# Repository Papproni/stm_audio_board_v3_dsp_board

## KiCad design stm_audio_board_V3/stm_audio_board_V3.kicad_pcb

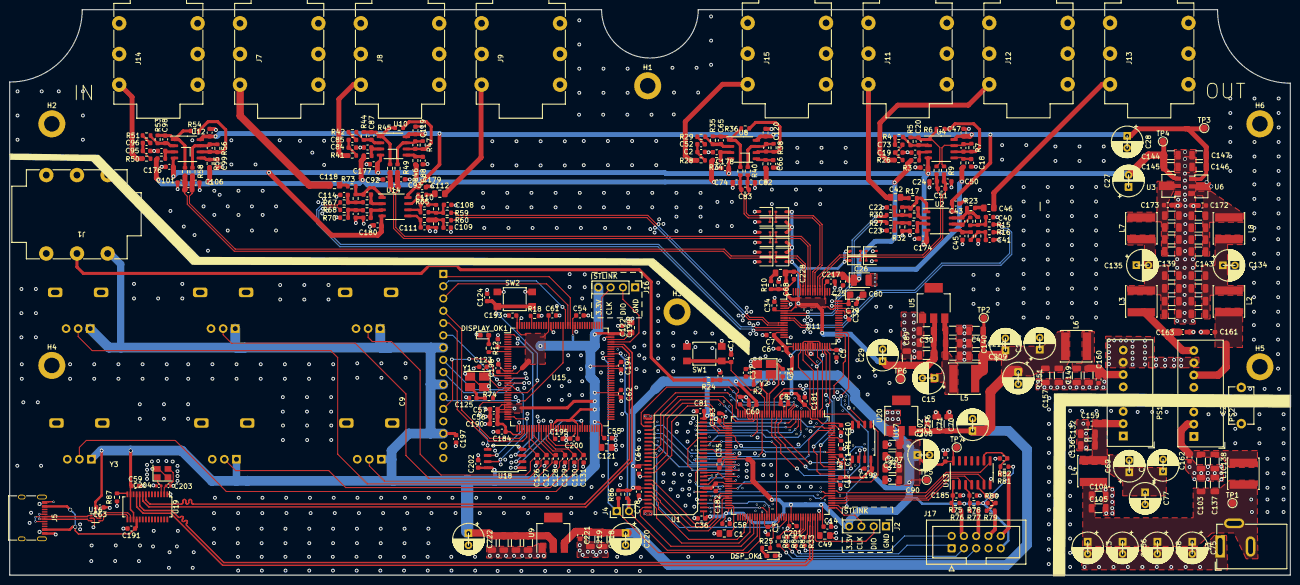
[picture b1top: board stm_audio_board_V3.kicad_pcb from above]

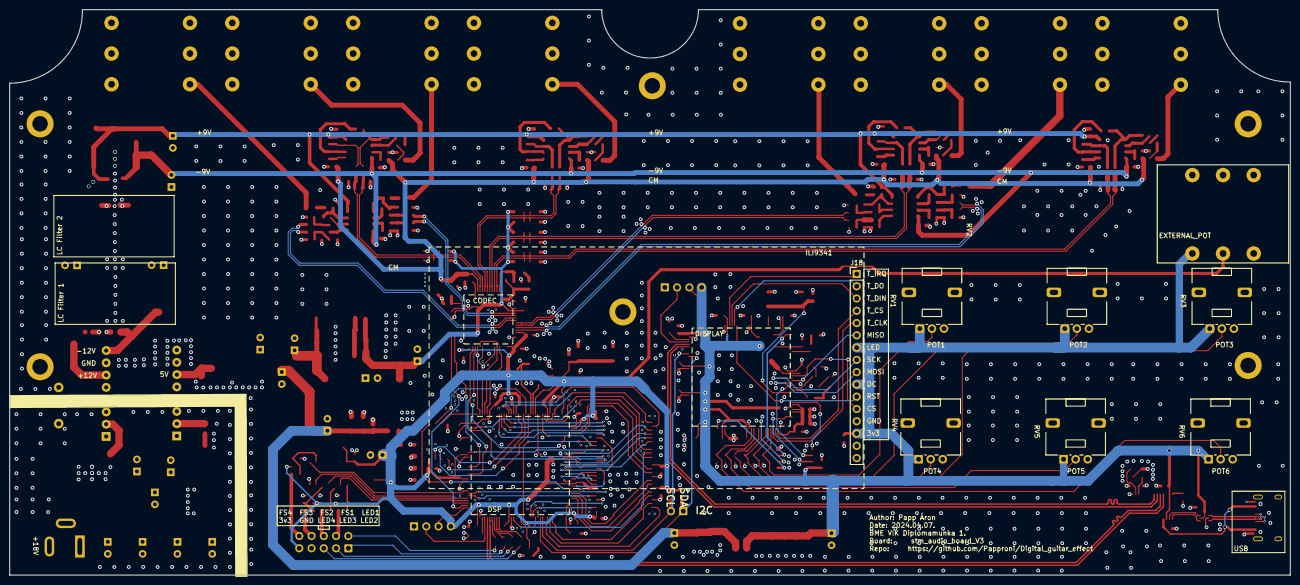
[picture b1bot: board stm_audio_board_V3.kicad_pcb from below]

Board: 4 copper layers, 265.0 x 117.0 mm, 404 parts (7 on the bottom side), 232 nets.

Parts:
C1, C42, C46, C49, C112, C118, C121, C122: 2.2uF; C_0805_2012Metric_Pad1.18x1.45mm_HandSolder
C2, C19, C21, C38, C39, C44, C45, C51, C72, C83, C84, C91, C94, C95, C100, C107, C110, C111, C116, C117: 100pF; C_0603_1608Metric
C3, C5, C6, C7, C8, C9, C10, C11, C12, C14, C16, C17, C18, C25, C32, C33, C34, C35, C36, C43, C47, C52, C53, C54, C55, C56, C57, C58, C59, C60, C61, C62, C63, C64, C66, C73, C78, C79, C81, C85, C86, C88, C96, C97, C99, C102, C113, C119, C120, C124, C126, C127, C128, C129, C130, C131, C159, C160, C161, C162, C163, C172, C173, C174, C175, C176, C177, C178, C179, C180, C181, C182, C183, C184, C185, C186, C187, C188, C189, C190, C191, C192, C193, C194, C195, C196, C197, C198, C199, C200, C201, C202, C217, C221, C227: 100nF; C_0603_1608Metric
C4, C30, C71, C89, C90, C103, C104, C105, C132, C133, C136, C137, C138, C139, C141, C142, C143, C144, C145, C146, C147, C148, C149, C152, C153, C154, C155, C157, C158, C164, C165, C166, C167, C168, C169, C170, C171, C205, C206, C207, C209, C210, C211, C212, C213, C214, C215, C216, C218, C219, C223, C224, C225, C226: 10uF; C_1206_3216Metric
C13, C15, C27, C28, C29, C48, C69, C70, C75, C76, C77, C134, C135, C140, C150, C151, C156, C208, C220, C222: 100uF; CP_Radial_D6.3mm_P2.50mm_reference_fix
C20, C65, C87, C98: 1p; C_0603_1608Metric
C22, C23, C40, C41, C108, C109, C114, C115: 470pF; C_0603_1608Metric
C24, C50, C68, C74, C82, C92, C93, C101, C106, C228: 1nF; C_0603_1608Metric
C26: 100uF tantal; CP_EIA-3528-21_Kemet-B
C31, C37, C123, C125: 12pF; C_0603_1608Metric
C67: 33nF; C_0805_2012Metric_Pad1.18x1.45mm_HandSolder
C80: 10uF tantal; CP_EIA-3216-18_Kemet-A
C203, C204: 20pF; C_0402_1005Metric
C229: 1nF; C_Disc_D7.5mm_W5.0mm_P7.50mm
D1, D4, D5, D6, D7, D8, D9, D12, D13, D14, D15, D16, D17, D18, D19, D20: 1N5819; D_SOD-323
DISPLAY_OK1: LED; LED_0603_1608Metric_Pad1.05x0.95mm_HandSolder
DSP_OK1: LED; LED_0603_1608Metric_Pad1.05x0.95mm_HandSolder
H1, H2, H3, H4, H5, H6: MountingHole_Pad; MountingHole_3.2mm_M3_DIN965_Pad
J1: External_POT; 6.3_jack_new_ref
J2: STlink_DSP; PinHeader_1x04_P2.54mm_Vertical
J3: Barrel_Jack_Switch; BarrelJack_GCT_DCJ200-10-A_Horizontal
J4: Conn_01x02_i2c; PinHeader_1x02_P2.54mm_Vertical
J5: USB_C_Receptacle_USB2.0; USB_C_Receptacle_XKB_U262-16XN-4BVC11
J7: AudioJack_LOOP1_SEND; 6.3_jack_new_ref
J8: AudioJack_LOOP1_RETURN; 6.3_jack_new_ref
J9: AudioJack_LOOP2_SEND; 6.3_jack_new_ref
J11: AudioJack_LOOP3_SEND; 6.3_jack_new_ref
J12: AudioJack_LOOP3_RETURN; 6.3_jack_new_ref
J13: AudioJack_OUTPUT; 6.3_jack_new_ref
J14: AudioJack_INPUT; 6.3_jack_new_ref
J15: AudioJack_LOOP2_RETURN; 6.3_jack_new_ref
J16: STlink_DISP_MCU; PinHeader_1x04_P2.54mm_Vertical
J17: Conn_01x10_Footswitch; IDC-Header_2x05_P2.54mm_Vertical
J18: Conn_01x16_ILI9341; PinHeader_1x16_P2.54mm_Vertical
L1, L2, L3, L4, L5, L6, L7, L8: 10uH; L_Sunlord_SWPA6020S
PS1: URB2405S-6WR3; Converter_DCDC_XP_POWER-ITxxxxxS_THT
PS2: WRA2412S-3WR2; Converter_DCDC_XP_POWER-ITxxxxxS_THT
R1, R18, R75, R78, R80, R82: 10k; R_0603_1608Metric
R2, R3, R8, R9, R11, R24, R26, R28, R34, R37, R39, R40, R41, R43, R46, R48, R49, R50, R52, R55, R57, R58, R74: 100R; R_0603_1608Metric
R4, R29, R42, R51: 1M; R_0603_1608Metric
R5, R35, R44, R53: 510k; R_0603_1608Metric
R6, R7, R36, R38, R45, R47, R54, R56: 4k7; R_0603_1608Metric
R10, R13, R14, R15, R16, R19, R20, R21, R22, R27, R30, R31, R32, R59, R60, R61, R62, R63, R64, R66, R67, R68, R69, R70, R71, R72, R86: 3k; R_0603_1608Metric
R12, R17, R23, R25, R33, R65, R73, R76, R77, R79, R81, R83, R84, R85: 1k; R_0603_1608Metric
R87: 2.7k; R_0603_1608Metric
RV1, RV2, RV3, RV4, RV5, RV6: R_Potentiometer; Potentiometer_Alps_RK09L_Single_Vertical
SW1, SW2: SW_SPST; SW_SPST_TL3305A
TP1: TestPoint_PWR_IN; TestPoint_Pad_D1.5mm
TP2: TestPoint_5V; TestPoint_Pad_D1.5mm
TP3: TestPoint_9V; TestPoint_Pad_D1.5mm
TP4: TestPoint_-9V; TestPoint_Pad_D1.5mm
TP5, TP7: TestPoint_3V3; TestPoint_Pad_D1.5mm
TP6: TestPoint_3V3A; TestPoint_Pad_D1.5mm
U1: IS42S16100H-7TL; TSOP-2-50-new
U2, U4, U8, U10, U12, U14: OP275; SSOP-8_3.9x5.05mm_P1.27mm
U3: 7909; SOT-89-3
U5, U9, U20: AP1117-33; SOT-223
U6: 7809; SOT-89-3
U7, U15: STM32H723ZGTx; LQFP-144_20x20mm_P0.5mm
U11: LQFP-64_10x10mm_P0.5mm
U13: 74HC14; SOIC-14_3.9x8.7mm_P1.27mm
U16: USBLC6-2P6; SOT-666
U17, U18: W25Q128JVS; SOIC-8_5.23x5.23mm_P1.27mm
U19: FE1.1s; SSOP-28_3.9x9.9mm_P0.635mm
Y1, Y2: X1E0000210132; Crystal_SMD_SeikoEpson_TSX3225-4Pin_3.2x2.5mm_HandSoldering
Y3: Crystal_GND24; Crystal_SMD_3225-4Pin_3.2x2.5mm

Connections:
5V: C4.1, C70.1, C71.1, C102.1, C140.1, C148.1, C150.1, C151.1, C157.1, C209.1, C210.1, C216.1, C218.1, C219.1, C220.1, C221.1, L5.1, L6.2, TP2.1, U9.3 (VI), U20.3 (VI)
+3.3V: C3.1, C5.1, C6.1, C7.1, C8.1, C9.1, C10.1, C11.1, C12.1, C14.1, C35.1, C36.1, C54.1, C55.1, C56.1, C57.1, C58.1, C59.1, C60.1, C61.1, C62.1, C63.1, C64.1, C78.1, C81.1, C90.1, C181.1, C182.1, C183.1, C184.1, C189.1, C190.1, C192.1, C193.1, C194.1, C195.1, C196.1, C197.1, C198.1, C199.1, C200.1, C201.1, C202.1, C207.1, C208.1, C214.1, C215.1, C222.1, C223.1, C224.1, C225.1, C226.1, J1.T, J2.4, J16.4, J17.9, J18.7, J18.10, J18.14, R66.1, R75.1, R78.1, R80.1, R82.1, R86.1, RV1.1, RV2.1, RV3.1, RV4.1, RV5.1, RV6.1, TP5.1, TP7.1, U1.1 (VDD), U1.7 (VDDQ), U1.13 (VDDQ), U1.25 (VDD), U1.38 (VDDQ), U1.44 (VDDQ), U7.6 (VBAT), U7.17 (VDD), U7.30 (VDD), U7.32 (VREF+), U7.33 (VDDA), U7.39 (VDD), U7.52 (VDD), U7.62 (VDD), U7.72 (VDD), U7.84 (VDD), U7.95 (VDD33USB), U7.108 (VDD), U7.121 (VDD), U7.131 (VDD), U7.144 (VDD), U9.2 (VO), U11.14 (PD/RST), U11.17 (DVDD), U11.32 (DVDD), U13.14 (VCC), U15.6 (VBAT), U15.17 (VDD), U15.30 (VDD), U15.32 (VREF+), U15.33 (VDDA), U15.39 (VDD), U15.52 (VDD), U15.62 (VDD), U15.72 (VDD), U15.84 (VDD), U15.95 (VDD33USB), U15.108 (VDD), U15.121 (VDD), U15.131 (VDD), U15.144 (VDD), U16.5 (VBUS), U17.8 (VCC), U18.8 (VCC), U19.13 (VD33), U19.17 (~XRSTJ), U20.2 (VO)
+3.3VA: C29.1, C30.1, C32.1, C33.1, C34.1, C68.1, C89.1, C205.1, C206.1, C217.1, C228.1, D4.1 (K), D5.1 (K), D7.1 (K), D9.1 (K), D13.1 (K), D15.1 (K), D17.1 (K), D19.1 (K), R10.2, TP6.1, U5.2 (VO), U11.5 (AVDD), U11.45 (AVDD), U11.51 (AVDD), U11.62 (AVDD)
+9V: C28.1, C43.1, C47.1, C113.1, C119.1, C120.1, C146.1, C147.1, C179.1, TP3.1, U2.8 (V+), U4.8 (V+), U6.1 (OUT), U8.8 (V+), U10.8 (V+), U12.8 (V+), U14.8 (V+)
-9V: C27.2, C144.1, C145.1, C174.2, C175.2, C176.2, C177.2, C178.2, C180.2, TP4.1, U2.4 (V-), U3.3 (VO), U4.4 (V-), U8.4 (V-), U10.4 (V-), U12.4 (V-), U14.4 (V-)
/Display_Interface/MCU_Display/DISPLAY_FLASH_CLK: U15.22 (PF10), U18.6 (CLK)
/Display_Interface/MCU_Display/DISPLAY_FLASH_CS: U15.64 (PE11), U18.1 (~CS)
/Display_Interface/MCU_Display/DISPLAY_FLASH_D0: U15.29 (PC3_C), U18.5 (DI(IO0))
/Display_Interface/MCU_Display/DISPLAY_FLASH_D1: U15.46 (PB0), U18.2 (DO(IO1))
/Display_Interface/MCU_Display/DISPLAY_FLASH_D2: U15.1 (PE2), U18.3 (IO2)
/Display_Interface/MCU_Display/DISPLAY_FLASH_D3: U15.35 (PA1), U18.7 (IO3)
/Display_Interface/MCU_Display/ILI9341_DISPLAY_CLK: J18.8, U15.19 (PF7)
/Display_Interface/MCU_Display/ILI9341_DISPLAY_CS: J18.12, U15.18 (PF6)
/Display_Interface/MCU_Display/ILI9341_DISPLAY_MISO: J18.6, U15.20 (PF8)
/Display_Interface/MCU_Display/ILI9341_DISPLAY_MOSI: J18.9, U15.21 (PF9)
/Display_Interface/MCU_Display/ILI9341_DISPLAY_RESET: J18.11, U15.125 (PG10)
/Display_Interface/MCU_Display/ILI9341_TOUCH_CLK: J18.5, U15.41 (PA5)
/Display_Interface/MCU_Display/ILI9341_TOUCH_CS: J18.4, U15.40 (PA4)
/Display_Interface/MCU_Display/ILI9341_TOUCH_IRQ: J18.1, U15.122 (PD6)
/Display_Interface/MCU_Display/ILI9341_TOUCH_MISO: J18.2, U15.124 (PG9)
/Display_Interface/MCU_Display/ILI9341_TOUCH_MOSI: J18.3, U15.123 (PD7)
/Display_Interface/MCU_Display/NRST_2: C124.1, SW2.1 (A), U15.25 (NRST)
/MCU/DSP_FLASH_CLK: U7.22 (PF10), U17.6 (CLK)
/MCU/DSP_FLASH_CS: U7.64 (PE11), U17.1 (~CS)
/MCU/DSP_FLASH_D0: U7.20 (PF8), U17.5 (DI(IO0))
/MCU/DSP_FLASH_D1: U7.21 (PF9), U17.2 (DO(IO1))
/MCU/DSP_FLASH_D2: U7.1 (PE2), U17.3 (IO2)
/MCU/DSP_FLASH_D3: U7.18 (PF6), U17.7 (IO3)
/MCU/DSP_SDRAM_ADRESS_BUS0: U1.21 (A0), U7.10 (PF0)
/MCU/DSP_SDRAM_ADRESS_BUS1: U1.22 (A1), U7.11 (PF1)
/MCU/DSP_SDRAM_ADRESS_BUS2: U1.23 (A2), U7.12 (PF2)
/MCU/DSP_SDRAM_ADRESS_BUS3: U1.24 (A3), U7.13 (PF3)
/MCU/DSP_SDRAM_ADRESS_BUS4: U1.27 (A4), U7.14 (PF4)
/MCU/DSP_SDRAM_ADRESS_BUS5: U1.28 (A5), U7.15 (PF5)
/MCU/DSP_SDRAM_ADRESS_BUS6: U1.29 (A6), U7.50 (PF12)
/MCU/DSP_SDRAM_ADRESS_BUS7: U1.30 (A7), U7.53 (PF13)
/MCU/DSP_SDRAM_ADRESS_BUS8: U1.31 (A8), U7.54 (PF14)
/MCU/DSP_SDRAM_ADRESS_BUS9: U1.32 (A9), U7.55 (PF15)
/MCU/DSP_SDRAM_ADRESS_BUS10: U1.20 (A10), U7.56 (PG0)
/MCU/DSP_SDRAM_ADRESS_BUS11: U1.19 (A11), U7.89 (PG4)
/MCU/DSP_SDRAM_CAS: U1.16 (/CAS), U7.132 (PG15)
/MCU/DSP_SDRAM_CKE: U1.34 (CKE), U7.29 (PC3_C)
/MCU/DSP_SDRAM_CLK: U1.35 (CLK), U7.93 (PG8)
/MCU/DSP_SDRAM_CS: U1.18 (/CS), U7.28 (PC2_C)
/MCU/DSP_SDRAM_DATA_BUS0: U1.2 (DQ0), U7.85 (PD14)
/MCU/DSP_SDRAM_DATA_BUS1: U1.3 (DQ1), U7.86 (PD15)
/MCU/DSP_SDRAM_DATA_BUS2: U1.5 (DQ2), U7.114 (PD0)
/MCU/DSP_SDRAM_DATA_BUS3: U1.6 (DQ3), U7.115 (PD1)
/MCU/DSP_SDRAM_DATA_BUS4: U1.8 (DQ4), U7.58 (PE7)
/MCU/DSP_SDRAM_DATA_BUS5: U1.9 (DQ5), U7.59 (PE8)
/MCU/DSP_SDRAM_DATA_BUS6: U1.11 (DQ6), U7.60 (PE9)
/MCU/DSP_SDRAM_DATA_BUS7: U1.12 (DQ7), U7.63 (PE10)
/MCU/DSP_SDRAM_DATA_BUS8: U1.39 (DQ8), U7.40 (PA4)
/MCU/DSP_SDRAM_DATA_BUS9: U1.40 (DQ9), U7.41 (PA5)
/MCU/DSP_SDRAM_DATA_BUS10: U1.42 (DQ10), U7.66 (PE13)
/MCU/DSP_SDRAM_DATA_BUS11: U1.43 (DQ11), U7.67 (PE14)
/MCU/DSP_SDRAM_DATA_BUS12: U1.45 (DQ12), U7.68 (PE15)
/MCU/DSP_SDRAM_DATA_BUS13: U1.46 (DQ13), U7.77 (PD8)
/MCU/DSP_SDRAM_DATA_BUS14: U1.48 (DQ14), U7.78 (PD9)
/MCU/DSP_SDRAM_DATA_BUS15: U1.49 (DQ15), U7.79 (PD10)
/MCU/DSP_SDRAM_LDQM: U1.14 (LDQM), U7.141 (PE0)
/MCU/DSP_SDRAM_RAS: U1.17 (/RAS), U7.49 (PF11)
/MCU/DSP_SDRAM_UDQM: U1.36 (UDQM), U7.142 (PE1)
/MCU/DSP_SDRAM_WE: U1.15 (/WE), U7.26 (PC0)
/MCU/NRST: C16.1, SW1.1 (A), U7.25 (NRST)
/MCU/USB_Conn_D+: J5.A6 (D+), J5.B6 (D+), U16.1 (I/O1)
/MCU/USB_Conn_D-: J5.A7 (D-), J5.B7 (D-), U16.3 (I/O2)
/Power/+12V: C161.1, L2.1, PS2.6 (+Vout)
/Power/-12V: C163.1, L3.1, PS2.8 (-Vout)
AD1939_CM: C25.2, C26.1, R3.2, R11.2, R34.2, R37.2, R43.2, R46.2, R52.2, R55.2, U11.52 (CM)
AD1939_FILTR: C79.2, C80.1, U11.47 (FILTR)
AD1939_LF: C67.2, C68.2, C228.2, U11.61 (LF)
AD1939_SAI1A_CK: U7.4 (PE5), U11.21 (DBCLK), U11.28 (ABCLK)
AD1939_SAI1A_SDO: U7.5 (PE6), U11.20 (DSDATA1)
AD1939_SAI1A_WS: U7.3 (PE4), U11.22 (DLRCLK), U11.29 (ALRCLK)
AD1939_SAI1B_SDI: U7.2 (PE3), U11.27 (ASDATA1)
AD1939_SPI_CLK: U7.126 (PG11), U11.34 (CCLK)
AD1939_SPI_CS: U7.110 (PA15(JTDI)), U11.35 (CLATCH)
AD1939_SPI_MISO: U7.42 (PA6), U11.31 (COUT)
AD1939_SPI_MOSI: U7.123 (PD7), U11.30 (CIN)
ADC1N: C24.2, C51.2, D5.2 (A), D6.1 (K), R8.1, U11.54 (ADC1LN)
ADC1P: C50.1, C51.1, D1.1 (K), D4.2 (A), R9.1, U11.53 (ADC1LP)
ADC2N: C74.2, C83.2, D7.2 (A), D8.1 (K), R39.1, U11.56 (ADC1RN)
ADC2P: C82.1, C83.1, D9.2 (A), D12.1 (K), R40.1, U11.55 (ADC1RP)
ADC3N: C92.2, C94.2, D17.2 (A), D18.1 (K), R48.1, U11.58 (ADC2LN)
ADC3P: C93.1, C94.1, D19.2 (A), D20.1 (K), R49.1, U11.57 (ADC2LP)
ADC4N: C101.2, C107.2, D13.2 (A), D14.1 (K), R57.1, U11.60 (ADC2RN)
ADC4P: C106.1, C107.1, D15.2 (A), D16.1 (K), R58.1, U11.59 (ADC2RP)
Audio_Loop1_Return: J8.T, R41.1
Audio_Loop1_Send: C118.2, J7.T
Audio_Loop2_Return: J15.T, R28.1
Audio_Loop2_Send: C112.2, J9.T
Audio_Loop3_Return: J12.T, R26.1
Audio_Loop3_Send: C42.2, J11.T
Audio_Main_Input: J14.T, R50.1
Audio_Main_Output: C46.2, J13.T
DAC1N: R15.1, U11.9 (OR3N)
DAC1P: R16.1, U11.8 (OR3P)
DAC2N: R27.1, U11.7 (OL3N)
DAC2P: R30.1, U11.6 (OL3P)
DAC3N: R67.1, U11.13 (OR4N)
DAC3P: R68.1, U11.12 (OR4P)
DAC4N: R60.1, U11.11 (OL4N)
DAC4P: R59.1, U11.10 (OL4P)
DISPLAY_OK_LED: R12.2, U15.8 (PC14)
DISPLAY_USB_HS_D+: U15.104 (PA12), U19.9 (DP2)
DISPLAY_USB_HS_D-: U15.103 (PA11), U19.8 (DM2)
DSP_OK_LED: R25.2, U7.90 (PG5)
DSP_USB_HS_D+: U7.104 (PA12), U19.11 (DP1)
DSP_USB_HS_D-: U7.103 (PA11), U19.10 (DM1)
EXT_POT_ADC: C227.1, R24.1, U7.36 (PA2)
Earth: C13.2, C48.2, C69.2, C75.2, C76.2, C77.2, C103.2, C104.2, C105.2, C132.2, C133.2, C136.2, C137.2, C138.2, C156.2, C159.2, C162.2, C229.1, J3.1, PS1.1 (-Vin), PS2.1 (-Vin)
Footswitch_1: J17.4, R76.1
Footswitch_1_INTERRUPT_PIN: U7.111 (PC10), U13.2
Footswitch_2: J17.6, R77.1
Footswitch_2_INTERRUPT_PIN: U7.112 (PC11), U13.4
Footswitch_3: J17.8, R79.1
Footswitch_3_INTERRUPT_PIN: U7.113 (PC12), U13.6
Footswitch_4: J17.10, R81.1
Footswitch_4_INTERRUPT_PIN: U7.116 (PD2), U13.8
GND: C1.2, C2.1, C3.2, C4.2, C5.2, C6.2, C7.2, C8.2, C9.2, C10.2, C11.2, C12.2, C14.2, C15.2, C16.2, C17.2, C18.2, C19.1, C22.1, C23.2, C24.1, C25.1, C26.2, C27.1, C28.2, C29.2, C30.2, C31.1, C32.2, C33.2, C34.2, C35.2, C36.2, C37.1, C38.1, C40.1, C41.2, C43.2, C45.1, C47.2, C49.2, C50.2, C53.2, C54.2, C55.2, C56.2, C57.2, C58.2, C59.2, C60.2, C61.2, C62.2, C63.2, C64.2, C66.2, C70.2, C71.2, C74.1, C78.2, C79.1, C80.2, C81.2, C82.2, C84.1, C86.2, C88.2, C89.2, C90.2, C92.1, C93.2, C95.1, C97.2, C99.2, C101.1, C102.2, C106.2, C108.1, C109.2, C111.1, C113.2, C114.1, C115.2, C117.1, C119.2, C120.2, C121.2, C122.2, C123.1, C124.2, C125.1, C126.2, C127.2, C128.2, C129.2, C130.2, C131.2, C134.2, C135.1, C139.2, C140.2, C141.2, C142.2, C143.2, C144.2, C145.2, C146.2, C147.2, C148.2, C149.2, C150.2, C151.2, C152.2, C153.2, C154.2, C155.2, C157.2, C158.2, C160.2, C161.2, C163.2, C164.2, C165.2, C166.2, C167.2, C168.2, C169.2, C170.2, C171.2, C172.2, C173.2, C174.1, C175.1, C176.1, C177.1, C178.1, C179.2, C180.1, C181.2, C182.2, C183.2, C184.2, C185.2, C186.2, C187.2, C188.2, C189.2, C190.2, C191.2, C192.2, C193.2, C194.2, C195.2, C196.2, C197.2, C198.2, C199.2, C200.2, C201.2, C202.2, C203.1, C204.2, C205.2, C206.2, C207.2, C208.2, C209.2, C210.2, C211.2, C212.2, C213.2, C214.2, C215.2, C216.2, C217.2, C218.2, C219.2, C220.2, C221.2, C222.2, C223.2, C224.2, C225.2, C226.2, C227.2, C229.2, D1.2 (A), D6.2 (A), D8.2 (A), D12.2 (A), D14.2 (A), D16.2 (A), D18.2 (A), D20.2 (A), DISPLAY_OK1.1 (K), DSP_OK1.1 (K), H1.1, H2.1, H3.1, H4.1, H5.1, H6.1, J1.RN, J1.S, J2.1, J5.A1 (GND), J5.A12 (GND), J5.B1 (GND), J5.B12 (GND), J8.TN, J12.TN, J14.TN, J15.TN, J16.1, J17.7, J18.13, PS1.7 (-Vout), PS2.7 (Common), R1.2, R18.2, R20.1, R32.1, R62.1, R70.1, R87.2, RV1.3, RV2.3, RV3.3, RV4.3, RV5.3, RV6.3, SW1.2 (B), SW2.2 (B), U1.4 (GNDQ), U1.10 (GNDQ), U1.26 (GND), U1.41 (GNDQ), U1.47 (GNDQ), U1.50 (GND), U3.1 (GND), U5.1 (GND), U6.2 (GND), U7.16 (VSS), U7.31 (VSSA), U7.38 (VSS), U7.51 (VSS), U7.61 (VSS), U7.83 (VSS), U7.94 (VSS), U7.107 (VSS), U7.120 (VSS), U7.130 (VSS), U7.143 (PDR_ON), U9.1 (GND), U11.1 (AGND), U11.4 (AGND), U11.16 (DGND), U11.23 (VSUPPLY), U11.24 (VSENSE), U11.25 (VDRIVE), U11.33 (DGND), U11.44 (AGND), U11.46 (AGND), U11.48 (AGND), U13.7 (GND), U15.16 (VSS), U15.31 (VSSA), U15.38 (VSS), U15.51 (VSS), U15.61 (VSS), U15.83 (VSS), U15.94 (VSS), U15.107 (VSS), U15.120 (VSS), U15.130 (VSS), U15.143 (PDR_ON), U16.2 (GND), U17.4 (GND), U18.4 (GND), U19.1 (VSS), U20.1 (GND), Y1.2, Y1.4, Y2.2, Y2.4, Y3.2, Y3.4
I2C_SCL: J4.2, R66.2, U7.81 (PD12), U15.100 (PA8)
I2C_SDA: J4.1, R86.2, U7.82 (PD13), U15.99 (PC9)
LED1: J17.2, R33.2
LED1_PIN: R33.1, U7.102 (PA10)
LED2: J17.1, R83.2
LED2_PIN: R83.1, U7.101 (PA9)
LED3: J17.3, R84.2
LED3_PIN: R84.1, U7.100 (PA8)
LED4: J17.5, R85.2
LED4_PIN: R85.1, U7.99 (PC9)
unnamed: C1.1, U7.71 (VCAP)
unnamed: C2.2, C52.2, R28.2
unnamed: C19.2, C73.2, R26.2
unnamed: C20.2, R5.1, R6.2, R8.2, U4.1
unnamed: C21.2, R7.1, R9.2, U4.7
unnamed: C22.2, R13.1, R30.2, R31.1
unnamed: C23.1, R14.2, R27.2, R32.2
unnamed: C37.2, R2.2, Y2.3
unnamed: C39.2, R17.2, R31.2, U2.1
unnamed: C40.2, R15.2, R19.1, R21.1
unnamed: C41.1, R16.2, R20.2, R22.2
unnamed: C42.1, R17.1
unnamed: C44.2, R19.2, R23.2, U2.7
unnamed: C46.1, R23.1
unnamed: C49.1, U7.106 (VCAP)
unnamed: C52.1, R29.2
unnamed: C65.2, R35.1, R36.2, R39.2, U8.1
unnamed: C67.1, R10.1
unnamed: C72.2, R38.1, R40.2, U8.7
unnamed: C73.1, R4.2
unnamed: C84.2, C85.2, R41.2
unnamed: C85.1, R42.2
unnamed: C87.2, R44.1, R45.2, R48.2, U10.1
unnamed: C91.2, R47.1, R49.2, U10.7
unnamed: C95.2, C96.2, R50.2
unnamed: C96.1, R51.2
unnamed: C98.2, R53.1, R54.2, R57.2, U12.1
unnamed: C100.2, R56.1, R58.2, U12.7
unnamed: C108.2, R59.2, R61.1, R63.1
unnamed: C109.1, R60.2, R62.2, R64.2
unnamed: C110.2, R61.2, R65.2, U14.7
unnamed: C112.1, R65.1
unnamed: C114.2, R67.2, R69.1, R71.1
unnamed: C115.1, R68.2, R70.2, R72.2
unnamed: C116.2, R69.2, R73.2, U14.1
unnamed: C118.1, R73.1
unnamed: C121.1, U15.71 (VCAP)
unnamed: C122.1, U15.106 (VCAP)
unnamed: C125.2, R74.2, Y1.3
unnamed: C134.1, C142.1, C143.1, C152.1, C153.1, L2.2, L8.1
unnamed: C135.2, C139.1, C141.1, C154.1, C155.1, L3.2, L7.1
unnamed: C185.1, R75.2, R76.2, U13.1
unnamed: C186.1, R77.2, R78.2, U13.3
unnamed: C187.1, R79.2, R80.2, U13.5
unnamed: C188.1, R81.2, R82.2, U13.9
unnamed: DISPLAY_OK1.2 (A), R12.1
unnamed: DSP_OK1.2 (A), R25.1
unnamed: J1.R, R24.2
unnamed: C69.1, C76.1, C77.1, C132.1, C136.1, C159.1, L4.2, PS1.2 (+Vin)
unnamed: C149.1, C158.1, C160.1, L6.1, PS1.6 (+Vout)
unnamed: C133.1, C138.1, C162.1, L1.2, PS2.2 (+Vin)
unnamed: C38.2, R14.1, U2.3 (+)
unnamed: C39.1, R13.2, U2.2 (-)
unnamed: C45.2, R22.1, U2.5 (+)
unnamed: C44.1, R21.2, U2.6 (-)
unnamed: C165.1, C166.1, C167.1, C168.1, C173.1, L7.2, U3.2 (VI)
unnamed: C17.1, R3.1, U4.3 (+)
unnamed: C20.1, R4.1, R5.2, U4.2 (-)
unnamed: C18.1, R11.1, U4.5 (+)
unnamed: C21.1, R6.1, R7.2, U4.6 (-)
unnamed: C15.1, C211.1, C212.1, C213.1, L5.2, U5.3 (VI)
unnamed: C164.1, C169.1, C170.1, C171.1, C172.1, L8.2, U6.3 (IN)
unnamed: R1.1, U7.138 (BOOT0)
unnamed: C53.1, R34.1, U8.3 (+)
unnamed: C65.1, R29.1, R35.2, U8.2 (-)
unnamed: C66.1, R37.1, U8.5 (+)
unnamed: C72.1, R36.1, R38.2, U8.6 (-)
unnamed: C86.1, R43.1, U10.3 (+)
unnamed: C87.1, R42.1, R44.2, U10.2 (-)
unnamed: C88.1, R46.1, U10.5 (+)
unnamed: C91.1, R45.1, R47.2, U10.6 (-)
unnamed: C97.1, R52.1, U12.3 (+)
unnamed: C98.1, R51.1, R53.2, U12.2 (-)
unnamed: C99.1, R55.1, U12.5 (+)
unnamed: C100.1, R54.1, R56.2, U12.6 (-)
unnamed: C117.2, R72.1, U14.3 (+)
unnamed: C116.1, R71.2, U14.2 (-)
unnamed: C111.2, R64.1, U14.5 (+)
unnamed: C110.1, R63.2, U14.6 (-)
unnamed: R18.1, U15.138 (BOOT0)
unnamed: U16.4 (I/O2), U19.15 (DMU)
unnamed: U16.6 (I/O1), U19.16 (DPU)
unnamed: R87.1, U19.14 (REXT)
unnamed: C191.1, J5.A4 (VBUS), J5.A9 (VBUS), J5.B4 (VBUS), J5.B9 (VBUS), U19.18 (VBUSM)
unnamed: C204.1, U19.3 (XIN), Y3.1
unnamed: C203.2, U19.2 (XOUT), Y3.3
OSC0: C31.2, U7.23 (PH0), Y2.1
OSC0_2: C123.2, U15.23 (PH0), Y1.1
OSC1: R2.1, U7.24 (PH1)
OSC1_2: R74.1, U15.24 (PH1)
POT1: C126.1, RV1.2, U15.42 (PA6)
POT2: C127.1, RV2.2, U15.43 (PA7)
POT3: C129.1, RV3.2, U15.47 (PB1)
POT4: C128.1, RV4.2, U15.44 (PC4)
POT5: C130.1, RV5.2, U15.49 (PF11)
POT6: C131.1, RV6.2, U15.50 (PF12)
PWR_INPUT_12V-18V: C13.1, C48.1, C75.1, C103.1, C104.1, C105.1, C137.1, C156.1, J3.2, J3.3, L1.1, L4.1, TP1.1
SWCLK_DISP: J16.3, U15.109 (PA14(JTCK)
SWCLK_DSP: J2.3, U7.109 (PA14(JTCK)
SWDIO_DISP: J16.2, U15.105 (PA13(JTMS)
SWDIO_DSP: J2.2, U7.105 (PA13(JTMS)

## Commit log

2024-02-25 Copies from old work
2024-02-26 SDRAM symbol added
2024-02-27 Footprint tsop-2-50 added
2024-02-27 new sdram footprint created
2024-02-27 pcb redesign
2024-03-03 Input and output stages are made and assembly started on pcb view
2024-03-06 Input output connected to codec
2024-03-08 minor changes
2024-03-17 +-12 DCDC added
2024-03-19 isolated power section done
2024-03-19 minor power section fixes
2024-03-19 safety commit
2024-03-21 Analog power and SDRAm routing reworked
2024-03-24 Footswitch debounce added
2024-03-24 USB added
2024-03-26 New orientation, Overvoltage protection added
2024-03-28 Testpoints and parts for usb hub added
2024-03-30 Reworked outline for enclosure
2024-03-30 1117 regulator added
2024-03-30 minor commit
2024-03-31 gnd vias added, footswitch mux connected
2024-04-02 added external pot, added feedback leds, added I2C between MCUs
2024-04-03 PCB design is finished
2024-04-06 minor changes to components
2024-04-07 added silkscreen captions, capacitor between gnd and earth
2024-04-07 gerber created
2024-04-08 Via size increased for economical reasons
